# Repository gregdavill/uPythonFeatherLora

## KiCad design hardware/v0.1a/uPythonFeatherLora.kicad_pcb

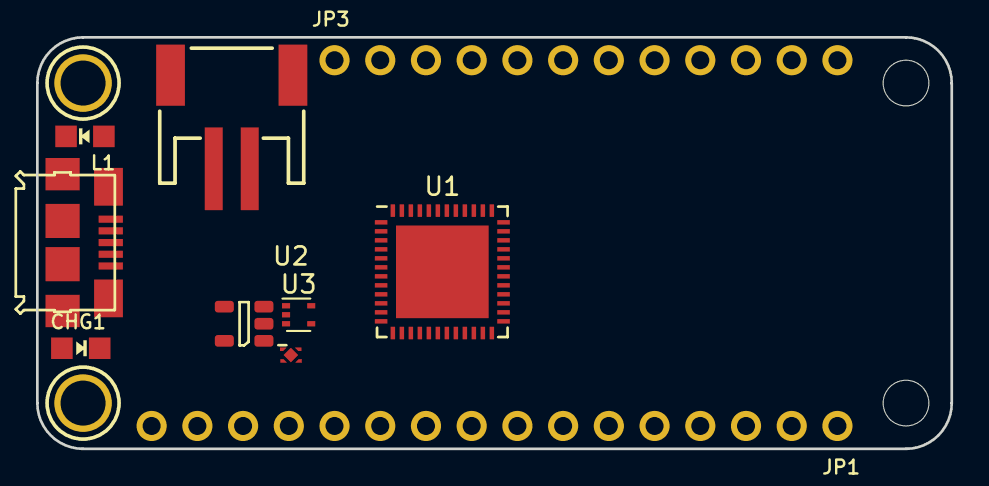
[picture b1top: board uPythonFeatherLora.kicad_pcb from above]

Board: 2 copper layers, 50.8 x 22.9 mm, 14 parts (0 on the bottom side), 3 nets, no tracks yet.

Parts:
@HOLE0, @HOLE1: (no value)
CHG1: ORANGE; CHIPLED_0805_NOOUTLINE
J3: USB_OTG; Connector_USB_Micro_B_SMD
J4: Conn_01x02_Male; S2B-PH-SM4-TB
JP1: HEADER-1X16ROUND; 1X16_ROUND
JP3: HEADER-1X12; 1X12_ROUND
L1: RED; CHIPLED_0805_NOOUTLINE
U1: ATSAMD51G19A; QFN-48-1EP_7x7mm_Pitch0.5mm
U2: NCP167; X2SON_4_1.0x1.0mm
U3: NUP2114; SOT-553
U4: MCP73832; SOT-23-5
U$31, U$32: MOUNTINGHOLE2.5; MOUNTINGHOLE_2.5_PLATED

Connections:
GND: JP1.13, L1.C
unnamed: U1.42, U1.49
VBUS: CHG1.A, JP3.3

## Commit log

2018-12-30 Add Submodules
2018-12-30 Started working on the new design.
